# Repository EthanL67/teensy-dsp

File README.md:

# teensy-dsp
Experimental pedal-format stereo effects processor using the Teensy 4.1 and Audio Shield. Hardware development currently in progress!

My design goals are as follows:
-	Reprogrammable stereo multi-effects console
-	Accepts instrument-level and line-level audio inputs
-	Runs on common 9V guitar pedal power supplies
-	Implementations of common audio effects:
    -	Saturation/distortion, fuzz
    -	Phaser, vibrato, chorus
    -	Digital delay, tape delay emulation
    -	Studio-quality reverb

# BOM
- [Teensy 4.1 Microcontroller](https://www.pjrc.com/store/teensy41.html)
- [Teensy Audio Shield](https://www.pjrc.com/store/teensy3_audio.html)

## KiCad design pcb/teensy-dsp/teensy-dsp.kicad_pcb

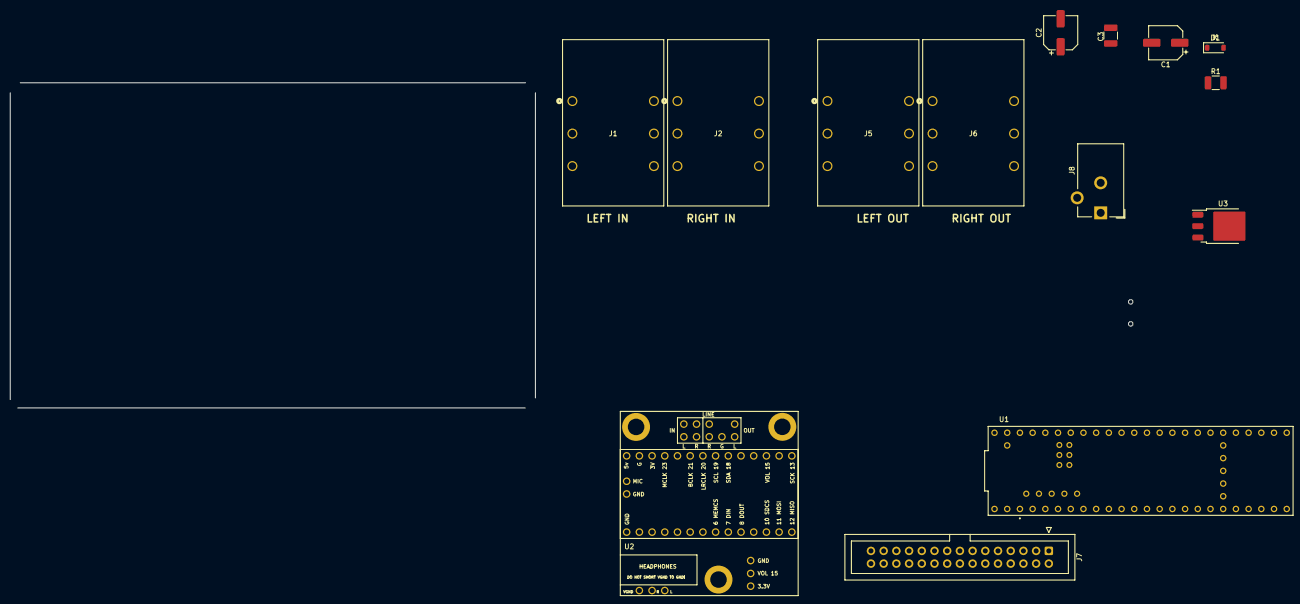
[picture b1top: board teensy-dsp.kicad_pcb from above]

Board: 4 copper layers, 105.0 x 65.0 mm, 15 parts (1 on the bottom side), 37 nets, no tracks yet.

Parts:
C1, C2: 100u 16V; CP_Elec_6.3x5.9
C3: 100n 16V; C_1210_3225Metric_Pad1.33x2.70mm_HandSolder
D1: D; D_SOD-123
J1, J2, J5, J6: ACJS-IH; ACJS-IH_AMP
J7: Conn_02x15_Odd_Even; IDC-Header_2x15_P2.54mm_Vertical
J8: Barrel_Jack_Switch; BarrelJack_CUI_PJ-102AH_Horizontal
J9: USB_B_Mini; USB_Mini-B_Wuerth_65100516121_Horizontal
R1: 47R; R_1210_3225Metric_Pad1.30x2.65mm_HandSolder
U1: Teensy4.1; MODULE_DEV-16771
U2: Teensy4.0_AudioShield_REVD; 4.0audioshield
U3: LM7805_TO220; TO-252-3_TabPin2

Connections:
+3.3V: J7.3, U1.3.3V_1 (3.3V), U1.3.3V_2 (3.3V__1), U1.3.3V_3 (3.3V__2), U2.28 (3V)
+5V: C2.1, C3.1, U1.VIN, U3.3 (VO)
+9V: C1.1, J7.1, R1.2, U3.1 (VI)
Audio BCLK: U1.21 (A7), U2.25 (21_A7_RX5_BCLK1)
Audio DIN: U1.7 (RX2), U2.9 (7_RX2_OUT1A)
Audio DOUT: U1.8 (TX2), U2.10 (8_TX2_IN1)
Audio LRCLK: U1.20 (A6), U2.24 (20_A6_TX5_LRCLK1)
Audio MCLK: U1.23 (A9), U2.27 (23_A9_CRX1_MCLK1)
Audio MEMCS: U1.6 (OUT1D), U2.8 (6_OUT1D)
Audio MISO: U1.12 (MISO), U2.14 (12_MISO_MQSL)
Audio MOSI: U1.11 (MOSI), U2.13 (11_MOSI_CTX1)
Audio SCK: U1.13 (SCK), U2.17 (13_SCK_CRX1_LED)
Audio SCL: U1.19 (A5), U2.23 (19_A5_SCL0)
Audio SDA: U1.18 (A4), U2.22 (18_A4_SDA0)
Audio SDCS: U1.10 (CS1), U2.12 (10_CS_MQSR)
FSW_1: J7.7, U1.28 (RX7)
FSW_2: J7.5, U1.29 (TX7)
GND: C1.2, C2.2, C3.2, J1.R, J2.R, J5.R, J6.R, J7.2, J7.4, J7.6, J7.8, J7.10, J7.12, J7.14, J7.16, J7.18, J7.20, J7.22, J7.24, J7.26, J7.28, J7.30, J8.1, J9.5 (GND), U1.GND1 (GND), U1.GND2 (GND__1), U1.GND3 (GND__2), U1.GND4 (GND__3), U1.GND5 (GND__4), U1.USB_GND1 (USB_GND), U1.USB_GND2 (USB_GND__1), U2.1 (GND), U2.29 (GND), U2.32 (LINE_OUT_GND), U2.36 (LINE_IN_R_GND), U2.37 (LINE_IN_L_GND), U3.2 (GND)
L Line In: J1.T, U2.35 (LINE_IN_L)
L Line Out: J5.T, U2.31 (LINE_OUT_L)
LED_BLANK: J7.15, U1.2 (OUT2)
LED_GSCLK: J7.9, U1.5 (IN2)
LED_SCLK: J7.11, U1.4 (BCLK2)
LED_SIN: J7.17, U1.9 (OUT1C)
LED_XLAT: J7.13, U1.3 (LRCLK2)
unnamed: D1.2 (A), J8.2
unnamed: D1.1 (K), R1.1
unnamed: J9.3 (D+), U1.D+
unnamed: J9.2 (D-), U1.D-
POT_1: J7.19, U1.27 (A13)
POT_2: J7.21, U1.26 (A12)
POT_3: J7.23, U1.25 (A11)
POT_4: J7.25, U1.24 (A10)
POT_5: J7.27, U1.38 (A14)
POT_6: J7.29, U1.39 (A15)
R Line In: J2.T, U2.34 (LINE_IN_R)
R Line Out: J6.T, U2.33 (LINE_OUT_R)

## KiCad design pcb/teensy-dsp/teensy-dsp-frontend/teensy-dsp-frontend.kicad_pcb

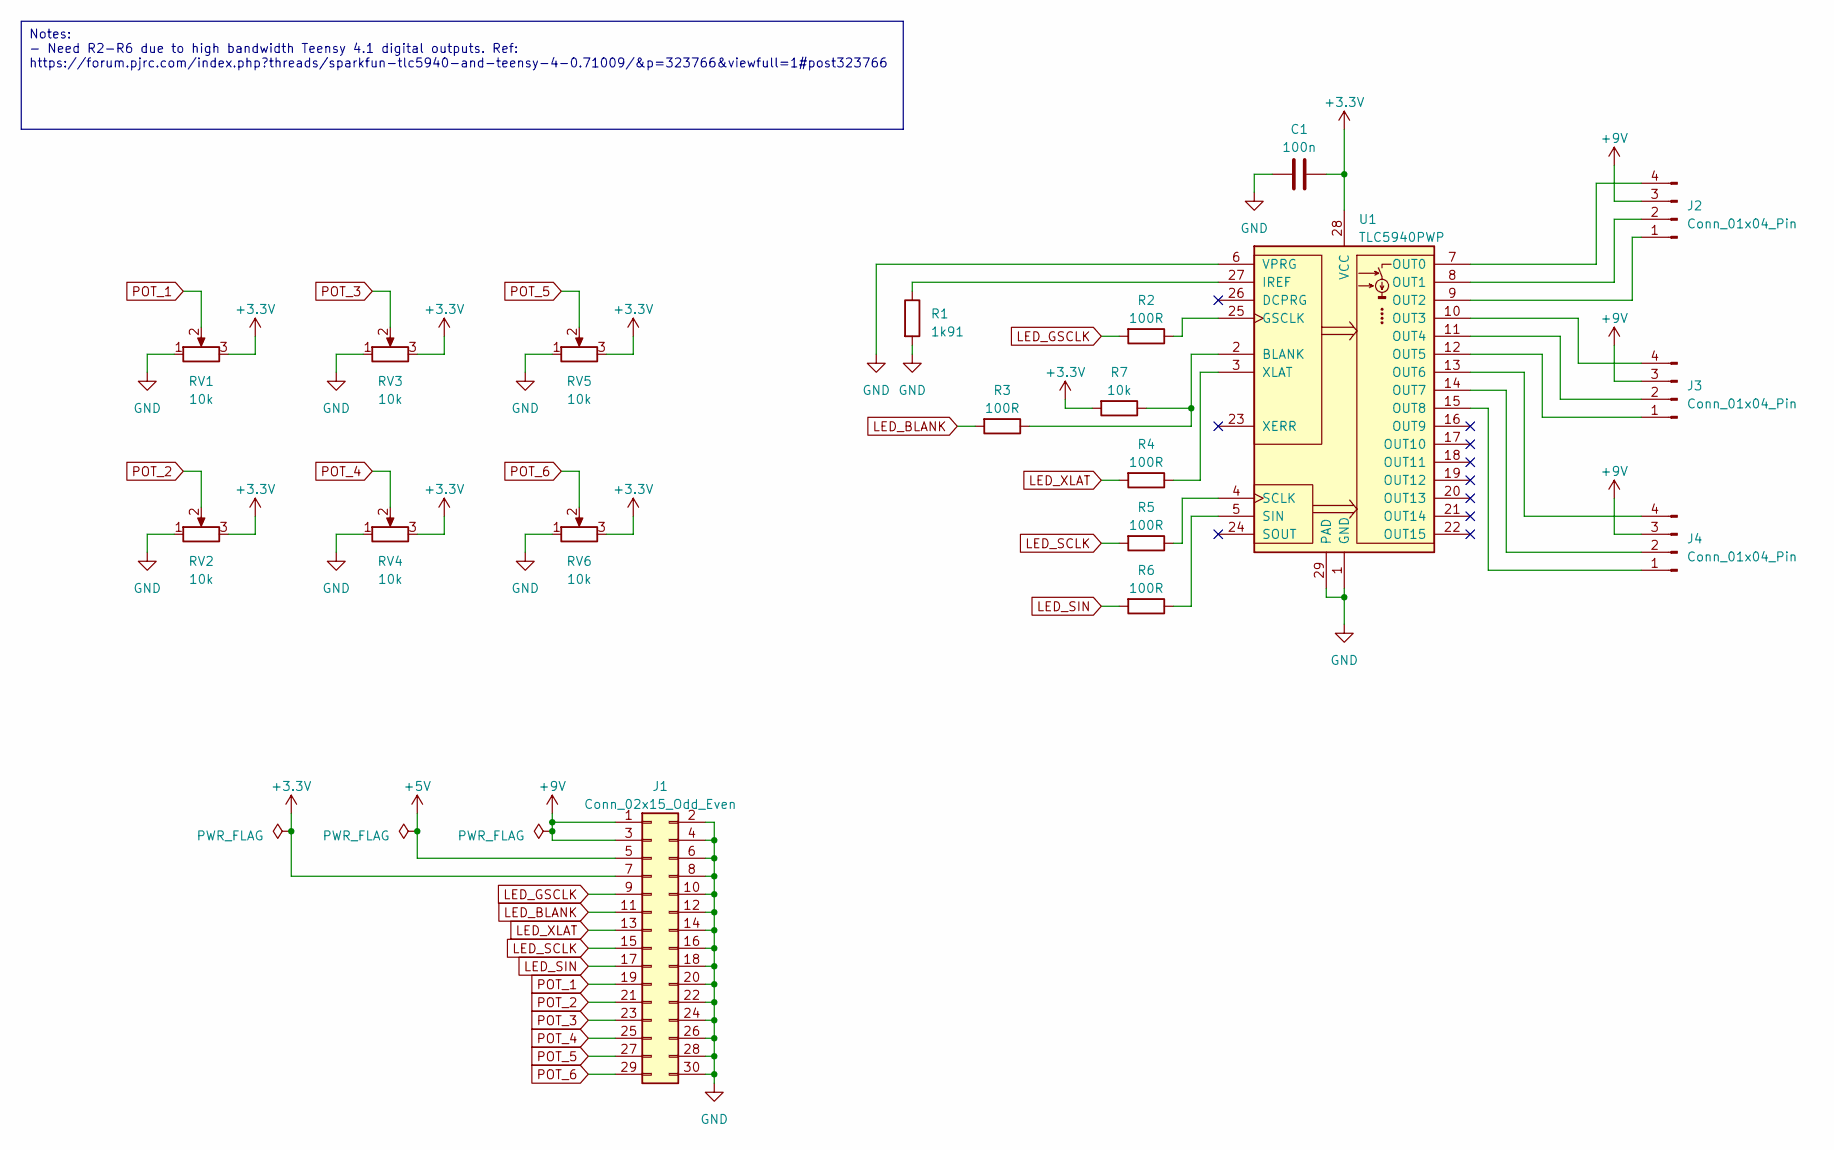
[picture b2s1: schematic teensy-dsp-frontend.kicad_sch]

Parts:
C1: 100n; C_1206_3216Metric_Pad1.33x1.80mm_HandSolder
J1: Conn_02x15_Odd_Even; IDC-Header_2x15_P2.54mm_Vertical
J2, J3, J4: Conn_01x04_Pin; PinHeader_1x04_P2.54mm_Horizontal
R1: 1k91; R_1206_3216Metric_Pad1.30x1.75mm_HandSolder
R2, R3, R4, R5, R6: 100R; R_1206_3216Metric_Pad1.30x1.75mm_HandSolder
R7: 10k; R_1206_3216Metric_Pad1.30x1.75mm_HandSolder
RV1, RV2, RV3, RV4, RV5, RV6: 10k; Potentiometer_TT_P0915N
U1: TLC5940PWP; HTSSOP-28-1EP_4.4x9.7mm_P0.65mm_EP3.4x9.5mm_Mask2.4x6.17mm_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

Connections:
+3.3V: C1.2, J1.7, R7.2, RV1.3, RV2.3, RV3.3, RV4.3, RV5.3, RV6.3, U1.28 (VCC)
+5V: J1.5
+9V: J1.1, J1.3, J2.3, J3.3, J4.3
GND: C1.1, J1.2, J1.4, J1.6, J1.8, J1.10, J1.12, J1.14, J1.16, J1.18, J1.20, J1.22, J1.24, J1.26, J1.28, J1.30, R1.2, RV1.1, RV2.1, RV3.1, RV4.1, RV5.1, RV6.1, U1.1 (GND), U1.6 (VPRG), U1.29 (PAD)
LED_BLANK: J1.11, R3.2
LED_GSCLK: J1.9, R2.2
LED_SCLK: J1.15, R5.2
LED_SIN: J1.17, R6.2
LED_XLAT: J1.13, R4.2
unnamed: J2.1, U1.9 (OUT2)
unnamed: J2.2, U1.8 (OUT1)
unnamed: J2.4, U1.7 (OUT0)
unnamed: J3.1, U1.12 (OUT5)
unnamed: J3.2, U1.11 (OUT4)
unnamed: J3.4, U1.10 (OUT3)
unnamed: J4.1, U1.15 (OUT8)
unnamed: J4.2, U1.14 (OUT7)
unnamed: J4.4, U1.13 (OUT6)
unnamed: R3.1, R7.1, U1.2 (BLANK)
unnamed: R2.1, U1.25 (GSCLK)
unnamed: R1.1, U1.27 (IREF)
unnamed: R5.1, U1.4 (SCLK)
unnamed: R6.1, U1.5 (SIN)
unnamed: R4.1, U1.3 (XLAT)
POT_1: J1.19, RV1.2
POT_2: J1.21, RV2.2
POT_3: J1.23, RV3.2
POT_4: J1.25, RV4.2
POT_5: J1.27, RV5.2
POT_6: J1.29, RV6.2

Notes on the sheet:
Notes: - Need R2-R6 due to high bandwidth Teensy 4.1 digital outputs. Ref: https://forum.pjrc.com/index.php?threads/sparkfun-tlc5940-and-teensy-4-0.71009/&p=323766&viewfull=1#post323766

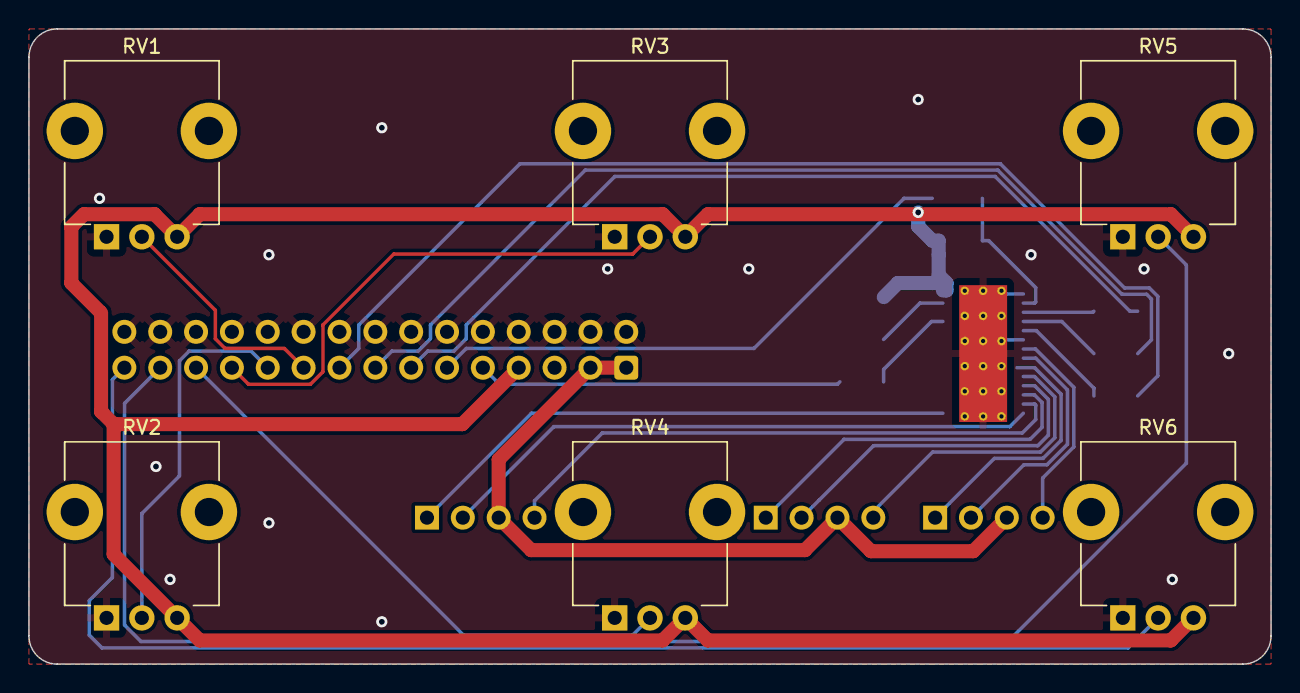
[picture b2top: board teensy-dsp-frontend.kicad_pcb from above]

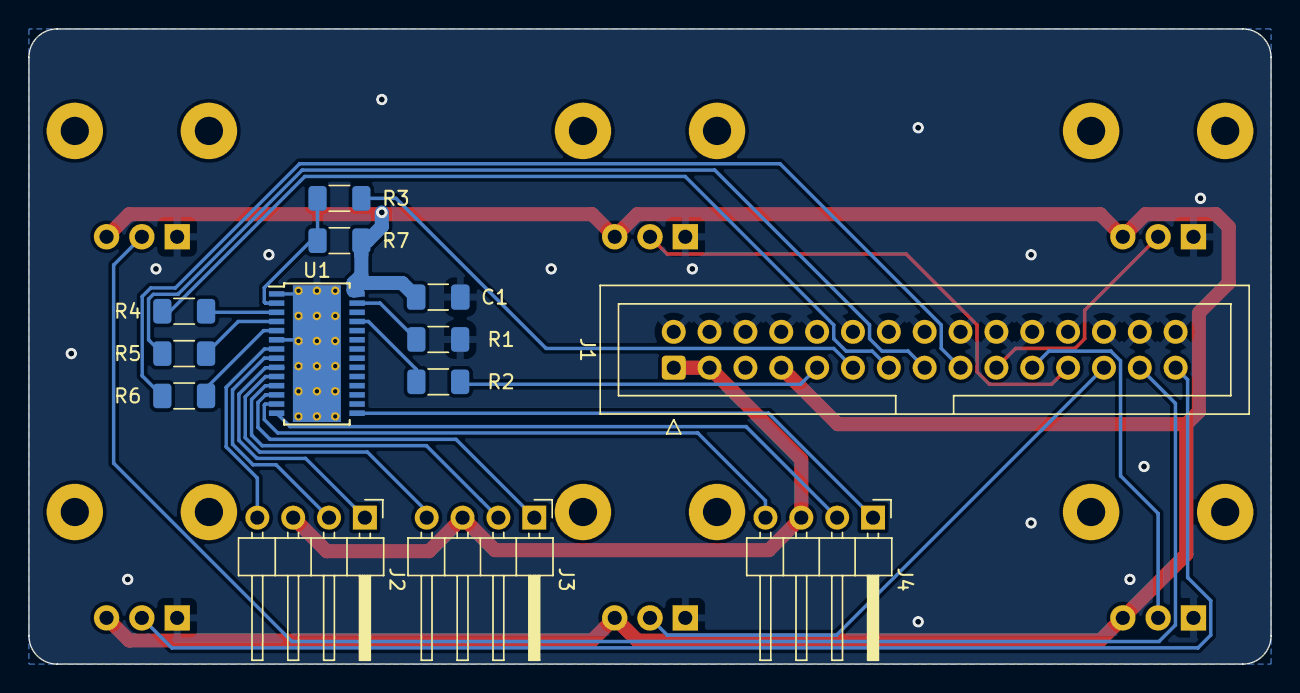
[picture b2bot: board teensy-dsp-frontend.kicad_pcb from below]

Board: 2 copper layers, 88.0 x 45.0 mm, 19 parts (13 on the bottom side), 29 nets.

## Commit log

2023-11-11 add initial organizational structure and platformio.init
2023-11-11 add main.cpp
2023-11-11 created platformio project
2023-11-11 added kicad project
2023-11-11 Added SolidWorks directory
2023-11-12 updated solidworks and kicad files
2023-11-12 update kicad and solidworks
2023-11-12 update gitignore
2023-11-12 added initial render
2023-11-12 remove temp files
2023-11-13 update renders
2023-11-13 added freeverb effect for testing
2023-11-14 update pcb layout
2023-11-17 pcb and case updates
2023-11-18 case updates
